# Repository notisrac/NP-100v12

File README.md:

# NP-100v12
My take on the [NP-100v12](http://diyaudioprojects.com/Solid/12AU7-IRF510-LM317-Headamp/) headphone amp (also it has a [GrubDac](http://www.diyforums.org/GrubDAC/GrubDACoverview.php) built in)

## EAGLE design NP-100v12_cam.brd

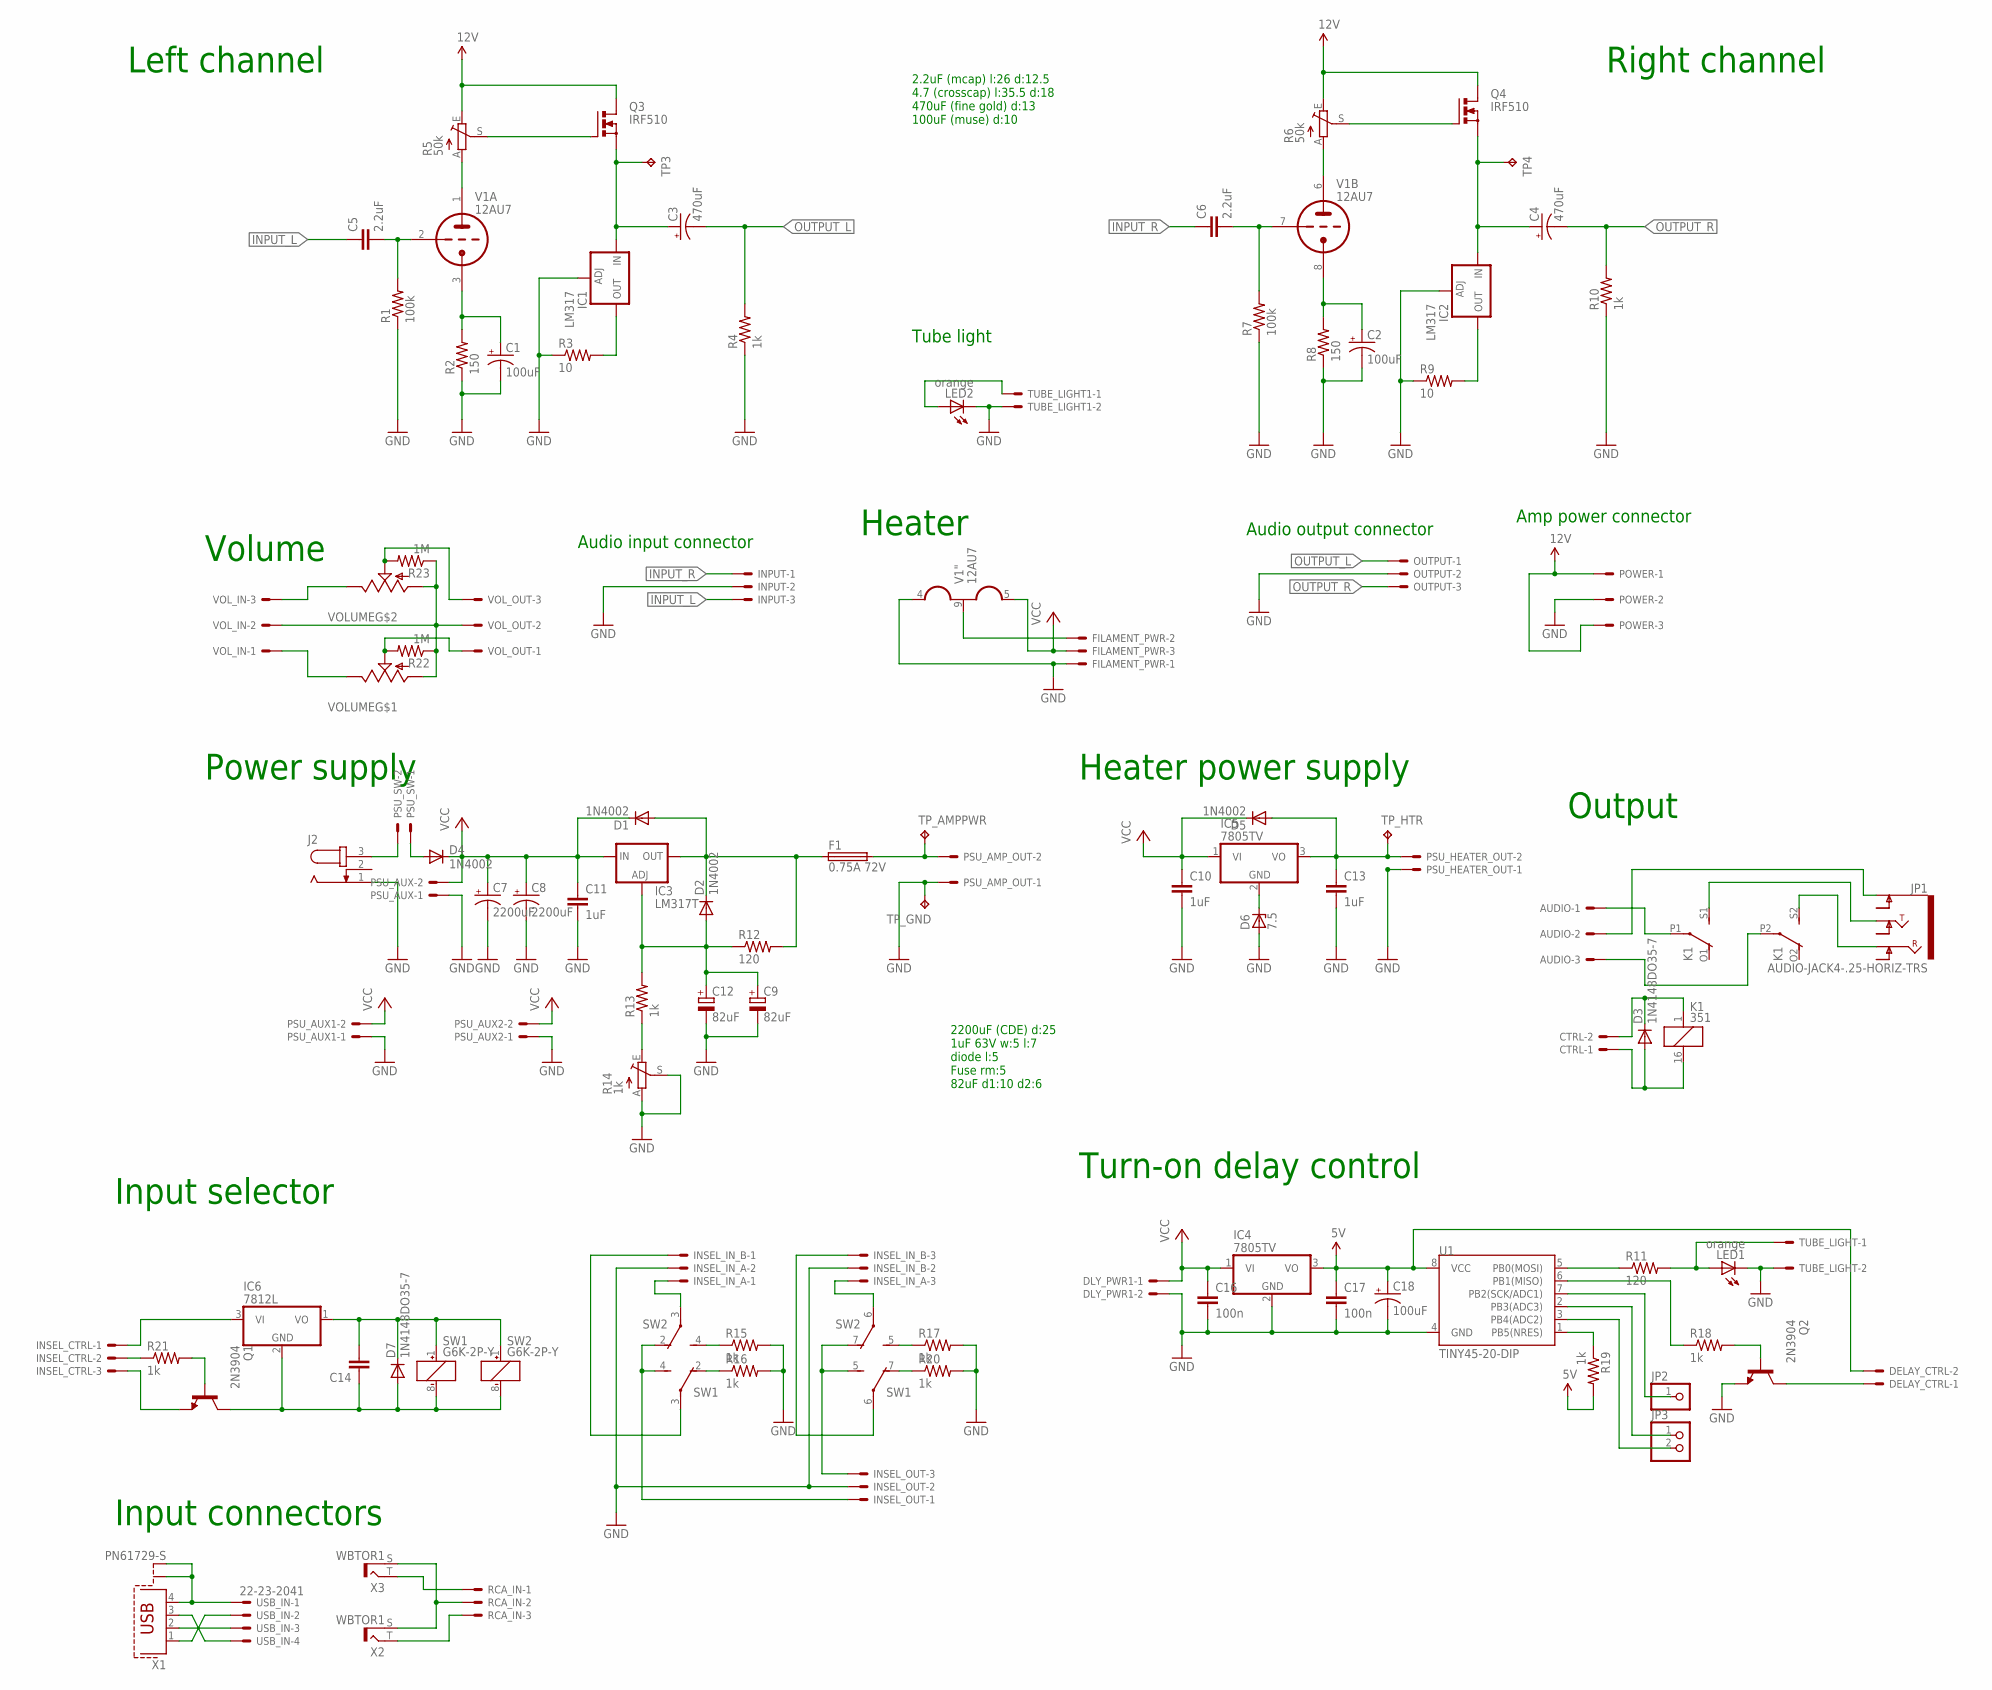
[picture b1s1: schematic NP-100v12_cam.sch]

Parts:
AUDIO: 22-23-2031
C1, C2: 100uF; E5-10,5
C3, C4: 470uF; E5-13
C5, C6: 2.2uF; C37.5B19
C7, C8: 2200uF; EB25D
C9: 82uF; E2,5-6
C10, C11, C13: 1uF; C5B4.5
C12: 82uF; E5-10,5
C14: C5/2.5; C5B2.5
C16, C17: 100n; CAP-PTH-5MM
C18: 100uF; E2,5-7
CTRL: 22-23-2021
D1, D2, D5: 1N4002; D-7.5
D3, D7: 1N4148DO35-7; DO35-7
D4: 1N4002; D-5
D6: 7.5; DO34Z7
DELAY_CTRL: 22-23-2021
DLY_PWR1: 22-23-2021
F1: 0.75A 72V; TE5
FILAMENT_PWR: 22-23-2031
IC1, IC2: LM317; 317TS
IC3: LM317T; 317TS
IC4, IC5: 7805TV; TO220V
IC6: 7812L; TO92
INPUT: 22-23-2031
INSEL_CTRL: 22-23-2031
INSEL_IN_A: 22-23-2031
INSEL_IN_B: 22-23-2031
INSEL_OUT: 22-23-2031
J2: JACK-PLUG0; SPC4077
JP1: AUDIO-JACK4-.25-HORIZ-TRS; AUDIO-JACK-.25-INCH-HORIZ-PTH
JP2: PINHD-1X1; 1X01
JP3: PINHD-1X2; 1X02
K1: 351
LED1, LED2: orange; LED3MM
OUTPUT: 22-23-2031
POWER: 22-23-2031
PSU_AMP_OUT: 22-23-2021
PSU_AUX, PSU_AUX1, PSU_AUX2: 22-23-2021
PSU_HEATER_OUT: 22-23-2021
PSU_SW: 22-23-2021
Q1, Q2: 2N3904; TO92
Q3, Q4: IRF510; TO220BV
R1, R7: 100k; 0207/10
R2, R8: 150; 0207/10
R3, R9: 10; 0207/10
R4, R10: 1k; 0207/10
R5, R6: 50k; SP19L
R11: 120; 0204/7
R12: 120; AXIAL-0.3
R13, R15, R16, R17, R20: 1k; AXIAL-0.3
R14: 1k; S64Y
R18, R19, R21: 1k; 0204/7
R22, R23: 1M; 0207/10
RCA_IN: 22-23-2031
SW1, SW2: G6K-2P-Y
TP3, TP4: TPPAD1-17; P1-17
TP_AMPPWR: TPPAD1-17; P1-17
TP_GND: TPPAD1-17; P1-17
TP_HTR: TPPAD1-17; P1-17
TUBE_LIGHT, TUBE_LIGHT1: 22-23-2021
U1: TINY45-20-DIP; DIP08
USB_IN: 22-23-2041
V1: 12AU7; NOVAL
VOLUME: ALPS_BLUE; ALPS_RK27
VOL_IN: 22-23-2031
VOL_OUT: 22-23-2031
X1: PN61729-S
X2, X3: WBTOR1

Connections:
5V: C17.1, C18.+, DELAY_CTRL.2, IC4.3 (VO), R19.2, U1.8 (VCC)
12V: POWER.1, POWER.3, Q3.D, Q4.D, R5.E, R6.E
GND: C1.-, C2.-, C7.-, C8.-, C9.-, C10.2, C11.2, C12.-, C13.2, C16.2, C17.2, C18.-, D6.A, DLY_PWR1.2, FILAMENT_PWR.1, IC1.1 (ADJ), IC2.1 (ADJ), IC4.2 (GND), INPUT.2, INSEL_IN_A.2, INSEL_IN_B.2, INSEL_OUT.2, J2.1, LED1.K (C), LED2.K (C), OUTPUT.2, POWER.2, PSU_AMP_OUT.1, PSU_AUX.1, PSU_AUX1.1, PSU_AUX2.1, PSU_HEATER_OUT.1, Q2.3 (E), R1.1, R2.1, R3.1, R4.1, R7.1, R8.1, R9.1, R10.1, R14.A, R14.S, R15.P$2 (2), R16.P$2 (2), R17.P$2 (2), R20.P$2 (2), TP_GND.TP, TUBE_LIGHT.2, TUBE_LIGHT1.2, U1.4 (GND), V1.4 (H1)
INPUT_L: C5.1, INPUT.3
INPUT_R: C6.1, INPUT.1
unnamed: C5.2, R1.2, V1.2 (TG)
unnamed: C1.+, R2.2, V1.3 (TK)
unnamed: R5.A, V1.1 (TA)
unnamed: Q3.G, R5.S
unnamed: C3.+, IC1.3 (IN), Q3.S, TP3.TP
unnamed: IC1.2 (OUT), R3.2
unnamed: C6.2, R7.2, V1.7 (TG)
unnamed: R11.1, U1.5 (PB0(MOSI))
unnamed: IC2.2 (OUT), R9.2
unnamed: C2.+, R8.2, V1.8 (TK)
unnamed: R6.A, V1.6 (TA)
unnamed: Q4.G, R6.S
unnamed: C4.+, IC2.3 (IN), Q4.S, TP4.TP
unnamed: D6.C, IC5.2 (GND)
unnamed: D1.A, D2.C, F1.1, IC3.2 (OUT), R12.P$2 (2)
unnamed: F1.2, PSU_AMP_OUT.2, TP_AMPPWR.TP
unnamed: C9.+, C12.+, D2.A, IC3.1 (ADJ), R12.P$1 (1), R13.P$2 (2)
unnamed: R13.P$1 (1), R14.E
unnamed: C13.1, D5.A, IC5.3 (VO), PSU_HEATER_OUT.2, TP_HTR.TP
unnamed: FILAMENT_PWR.2, V1.9 (H2)
unnamed: AUDIO.1, K1.P1
unnamed: CTRL.1, D3.A, K1.16 (2)
unnamed: R15.P$1 (1), SW2.4 (S)
unnamed: LED2.A, TUBE_LIGHT1.1
unnamed: C14.2, D7.C, IC6.1 (VO), SW1.1 (+), SW2.1 (+)
unnamed: R16.P$1 (1), SW1.2 (O)
unnamed: AUDIO.3, K1.P2
unnamed: JP1.TIP, K1.S1 (S)
unnamed: AUDIO.2, JP1.SLEEVE (EARTH)
unnamed: JP1.RING, K1.S2 (S)
unnamed: VOLUME.I2 (3), VOL_IN.3
unnamed: R22.1, R23.1, VOLUME.G1 (1), VOLUME.G2 (1), VOL_IN.2, VOL_OUT.2
unnamed: VOLUME.I1 (3), VOL_IN.1
unnamed: R23.2, VOLUME.O2 (2), VOL_OUT.3
unnamed: R22.2, VOLUME.O1 (2), VOL_OUT.1
unnamed: J2.3, PSU_SW.2
unnamed: CTRL.2, D3.C, K1.1
unnamed: LED1.A, R11.2, TUBE_LIGHT.1
unnamed: R17.P$1 (1), SW2.5 (S)
unnamed: R18.1, U1.6 (PB1(MISO))
unnamed: Q2.2 (B), R18.2
unnamed: DELAY_CTRL.1, Q2.1 (C)
unnamed: JP2.1, U1.7 (PB2(SCK/ADC1))
unnamed: R19.1, U1.1 (PB5(NRES))
unnamed: JP3.1, U1.2 (PB3(ADC3))
unnamed: JP3.2, U1.3 (PB4(ADC2))
unnamed: D4.A, PSU_SW.1
unnamed: R20.P$1 (1), SW1.7 (O)
unnamed: INSEL_IN_A.1, SW2.3
unnamed: INSEL_IN_A.3, SW2.6
unnamed: INSEL_IN_B.1, SW1.3
unnamed: INSEL_IN_B.3, SW1.6
unnamed: INSEL_OUT.3, SW1.5 (S), SW2.7 (O)
unnamed: INSEL_OUT.1, SW1.4 (S), SW2.2 (O)
unnamed: Q1.2 (B), R21.2
unnamed: IC6.3 (VI), INSEL_CTRL.1
unnamed: INSEL_CTRL.2, R21.1
unnamed: INSEL_CTRL.3, Q1.3 (E)
unnamed: C14.1, D7.A, IC6.2 (GND), Q1.1 (C), SW1.8 (-), SW2.8 (-)
unnamed: RCA_IN.2, X2.S, X3.S
unnamed: RCA_IN.1, X3.T
unnamed: RCA_IN.3, X2.T
unnamed: USB_IN.1, X1.4, X1.S1, X1.S2
unnamed: USB_IN.4, X1.3
unnamed: USB_IN.3, X1.2
unnamed: USB_IN.2, X1.1
OUTPUT_L: C3.-, OUTPUT.1, R4.2
OUTPUT_R: C4.-, OUTPUT.3, R10.2
VCC: C7.+, C8.+, C10.1, C11.1, C16.1, D1.C, D4.C, D5.C, DLY_PWR1.1, FILAMENT_PWR.3, IC3.3 (IN), IC4.1 (VI), IC5.1 (VI), PSU_AUX.2, PSU_AUX1.2, PSU_AUX2.2, V1.5 (H3)

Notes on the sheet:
2200uF (CDE) d:25 1uF 63V w:5 l:7 diode l:5 Fuse rm:5 82uF d1:10 d2:6
2.2uF (mcap) l:26 d:12.5 4.7 (crosscap) l:35.5 d:18 470uF (fine gold) d:13 100uF (muse) d:10
Left channel
Right channel
Volume
Heater
Power supply
Heater power supply
Turn-on delay control
Output
Audio input connector
Audio output connector
Amp power connector
Tube light
Input selector
Input connectors

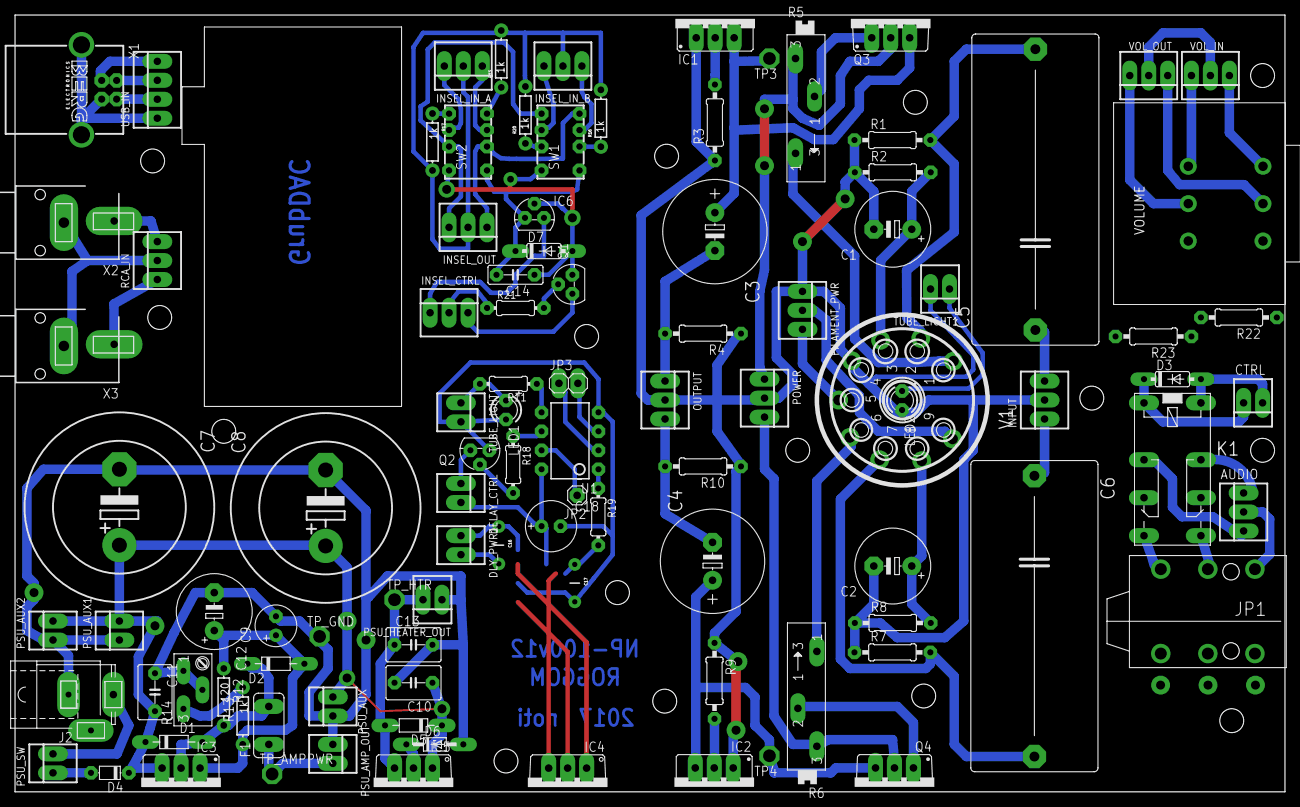
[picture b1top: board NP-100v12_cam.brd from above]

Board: 2 copper layers, 169.9 x 103.9 mm, 102 parts (0 on the bottom side), 74 nets.

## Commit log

2018-01-13 - Added resistor between the wiper and ground of the volume pot
    - Added missing ground connection to the volume pot
2018-01-14 - Added code for the turn on delay
    - Added arduino/visual micro/visual studio specific info to the gitignore file
2018-01-15 - Renamed the test points to reflect their function
2018-07-28 Added GA beacon to the README

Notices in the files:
parts and their libraries:
SparkFun-Connectors: Licensing: Creative Commons ShareAlike 4.0 International - https://creativecommons.org/licenses/by-sa/4.0
